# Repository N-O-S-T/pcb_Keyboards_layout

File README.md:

# pcb_Keyboards_layout

## [中文版](./README_CN.md)

## This is my first show

The keyboard layout of Poker is fun,61 keys are necessary.

## The PCB is using for testing.

Please do not use it for anywhere or anything, this program is still immature for the time being.

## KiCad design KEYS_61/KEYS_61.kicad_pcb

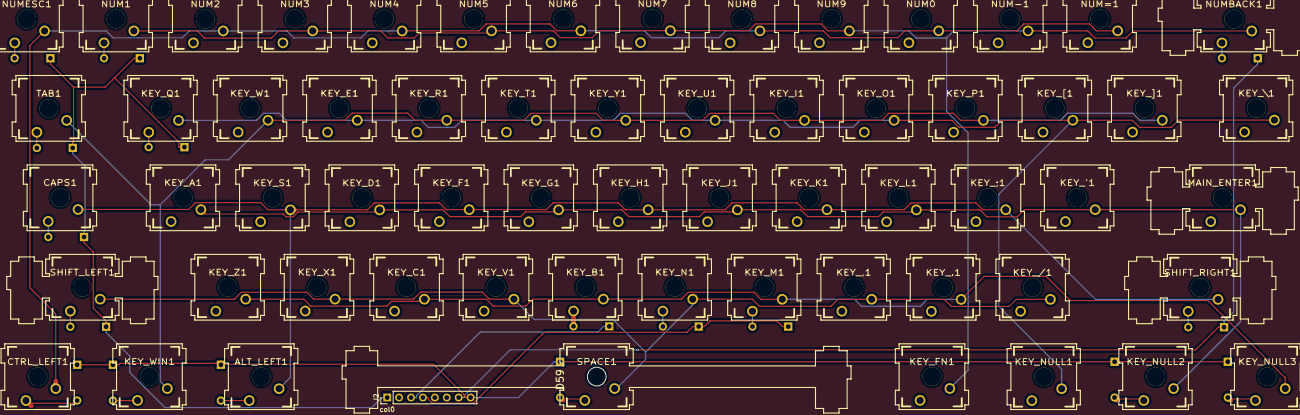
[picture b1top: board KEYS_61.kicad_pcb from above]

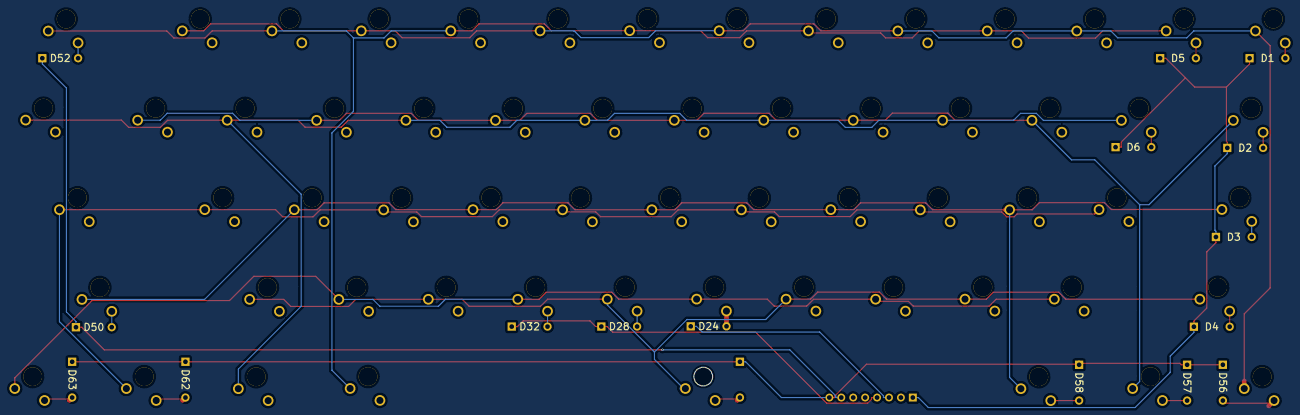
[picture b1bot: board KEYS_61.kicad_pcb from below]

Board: 2 copper layers, 79 parts (16 on the bottom side), 30 nets.

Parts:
ALT_LEFT1: KEY_WIN; CHERRY_PCB_125H
CAPS1: CAPS; CHERRY_PCB_175H
CTRL_LEFT1: CTRL_LEFT; CHERRY_PCB_125H
D1, D2, D3, D4, D5, D6, D24, D28, D32, D50, D52, D56, D57, D58, D59, D62, D63: 1N914WT; CHERRY_MX_DIODE
J2: Screw_Terminal_01x08; PinHeader_1x08_P2.54mm_Vertical
KEY_'1: KEY_'; CHERRY_PCB_100H
KEY_,1: KEY_,; CHERRY_PCB_100H
KEY_.1: KEY_.; CHERRY_PCB_100H
KEY_/1: KEY_/; CHERRY_PCB_100H
KEY_;1: KEY_;; CHERRY_PCB_100H
KEY_A1: KEY_A; CHERRY_PCB_100H
KEY_B1: KEY_B; CHERRY_PCB_100H
KEY_C1: KEY_C; CHERRY_PCB_100H
KEY_D1: KEY_D; CHERRY_PCB_100H
KEY_E1: KEY_E; CHERRY_PCB_100H
KEY_F1: KEY_F; CHERRY_PCB_100H
KEY_FN1: KEY_FN; CHERRY_PCB_125H
KEY_G1: KEY_G; CHERRY_PCB_100H
KEY_H1: KEY_H; CHERRY_PCB_100H
KEY_I1: KEY_I; CHERRY_PCB_100H
KEY_J1: KEY_J; CHERRY_PCB_100H
KEY_K1: KEY_K; CHERRY_PCB_100H
KEY_L1: KEY_L; CHERRY_PCB_100H
KEY_M1: KEY_M; CHERRY_PCB_100H
KEY_N1: KEY_N; CHERRY_PCB_100H
KEY_NULL1: KEY_NULL1; CHERRY_PCB_125H
KEY_NULL2: KEY_NULL2; CHERRY_PCB_125H
KEY_NULL3: KEY_NULL3; CHERRY_PCB_125H
KEY_O1: KEY_O; CHERRY_PCB_100H
KEY_P1: KEY_P; CHERRY_PCB_100H
KEY_Q1: KEY_Q; CHERRY_PCB_100H
KEY_R1: KEY_R; CHERRY_PCB_100H
KEY_S1: KEY_S; CHERRY_PCB_100H
KEY_T1: KEY_T; CHERRY_PCB_100H
KEY_U1: KEY_U; CHERRY_PCB_100H
KEY_V1: KEY_V; CHERRY_PCB_100H
KEY_W1: KEY_W; CHERRY_PCB_100H
KEY_WIN1: KEY_WIN; CHERRY_PCB_125H
KEY_X1: KEY_X; CHERRY_PCB_100H
KEY_Y1: KEY_Y; CHERRY_PCB_100H
KEY_Z1: KEY_Z; CHERRY_PCB_100H
KEY_[1: KEY_[; CHERRY_PCB_100H
KEY_\1: KEY_\; CHERRY_PCB_150H
KEY_]1: KEY_]; CHERRY_PCB_100H
MAIN_ENTER1: MAIN_ENTER; CHERRY_PCB_225H
NUM0: NUM0; CHERRY_PCB_100H
NUM1: NUM1; CHERRY_PCB_100H
NUM2: 2; CHERRY_PCB_100H
NUM3: NUM3; CHERRY_PCB_100H
NUM4: NUM4; CHERRY_PCB_100H
NUM5: NUM5; CHERRY_PCB_100H
NUM6: 6; CHERRY_PCB_100H
NUM7: NUM7; CHERRY_PCB_100H
NUM8: NUM8; CHERRY_PCB_100H
NUM9: NUM9; CHERRY_PCB_100H
NUM-1: NUM-; CHERRY_PCB_100H
NUM=1: NUM=; CHERRY_PCB_100H
NUMBACK1: NUMBACK; CHERRY_PCB_200H
NUMESC1: CHERRY_PCB_100H
SHIFT_LEFT1: SHIFT_LEFT; CHERRY_PCB_225H
SHIFT_RIGHT1: SHIFT_RIGHT; CHERRY_PCB_275H
SPACE1: SPACE; CHERRY_PLATE_625H
TAB1: TAB; CHERRY_PCB_150H

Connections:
/col0: D1.2, D2.2, D3.2, D4.2, D5.2, D6.2, J2.1
/col2: D24.2, J2.3
/col3: D28.2, D32.2, J2.4
/col6: D50.2, D52.2, J2.7
/col7: D56.2, D57.2, D58.2, D59.2, D62.2, D63.2, J2.8
/row0: CTRL_LEFT1.2, NUM0.2, NUM2.2, NUM4.2, NUM6.2, NUM8.2, NUM=1.2, NUMESC1.2
/row1: KEY_I1.2, KEY_P1.2, KEY_R1.2, KEY_W1.2, KEY_WIN1.2, KEY_Y1.2, KEY_]1.2, TAB1.2
/row2: ALT_LEFT1.2, CAPS1.2, KEY_;1.2, KEY_F1.2, KEY_H1.2, KEY_K1.2, KEY_S1.2, SHIFT_RIGHT1.2
/row3: KEY_,1.2, KEY_/1.2, KEY_N1.2, KEY_V1.2, KEY_X1.2, SHIFT_LEFT1.2, SPACE1.2
/row4: KEY_FN1.2, NUM1.2, NUM3.2, NUM5.2, NUM7.2, NUM9.2, NUM-1.2, NUMBACK1.2
/row5: KEY_E1.2, KEY_NULL1.2, KEY_O1.2, KEY_Q1.2, KEY_T1.2, KEY_U1.2, KEY_[1.2, KEY_\1.2
/row6: KEY_'1.2, KEY_A1.2, KEY_D1.2, KEY_G1.2, KEY_J1.2, KEY_L1.2, KEY_NULL2.2, MAIN_ENTER1.2
/row7: KEY_.1.2, KEY_B1.2, KEY_C1.2, KEY_M1.2, KEY_NULL3.2, KEY_Z1.2
unnamed: ALT_LEFT1.1, D58.1
unnamed: CAPS1.1, D3.1
unnamed: CTRL_LEFT1.1, D56.1
unnamed: D1.1, NUMESC1.1
unnamed: D2.1, TAB1.1
unnamed: D4.1, SHIFT_LEFT1.1
unnamed: D5.1, NUM1.1
unnamed: D6.1, KEY_Q1.1
unnamed: D24.1, KEY_B1.1
unnamed: D28.1, KEY_N1.1
unnamed: D32.1, KEY_M1.1
unnamed: D50.1, SHIFT_RIGHT1.1
unnamed: D52.1, NUMBACK1.1
unnamed: D57.1, KEY_WIN1.1
unnamed: D59.1, SPACE1.1
unnamed: D62.1, KEY_NULL2.1
unnamed: D63.1, KEY_NULL3.1

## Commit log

2019-11-11 keyboard_61_layout_pcb
2019-11-11 Create README.md
    Readme_US
2019-11-11 PCB_Cu
2019-11-11 CHERRY_MX
2019-11-11 PCB 布局
2019-11-11 PCB 自动布线参考
2019-11-11 发布 Gerber 文件
2019-11-12 手动布线更改
2019-11-12 更改钻孔信息
2019-11-13 更改部分走线
